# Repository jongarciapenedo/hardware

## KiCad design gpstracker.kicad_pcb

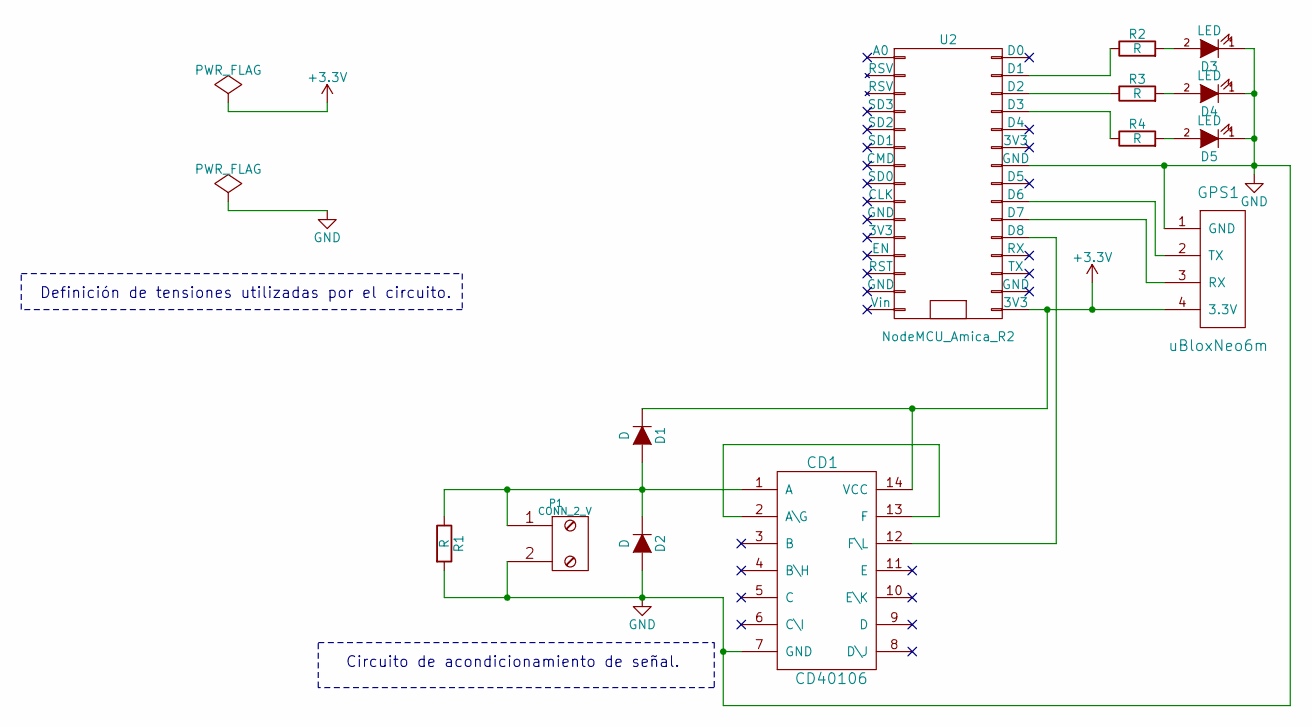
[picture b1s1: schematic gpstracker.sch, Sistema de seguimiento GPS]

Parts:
CD1: CD40106; DIP-14_W7.62mm
D1, D2: D; Diode_DO-35_SOD27_Horizontal_RM10
D3, D4, D5: LED; LED-5MM
GPS1: uBloxNeo6m; Pin_Header_Straight_1x04
P1: CONN_2_V; bornier2_V
R1, R2, R3, R4: R; Resistor_Horizontal_RM10mm
U2: NodeMCU_Amica_R2

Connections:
+3V3: CD1.14 (VCC), D1.1 (K), GPS1.4 (3.3V), U2.16 (3V3)
GND: CD1.7 (GND), D2.2 (A), D3.1 (K), D4.1 (K), D5.1 (K), GPS1.1 (GND), P1.2, R1.2, U2.24 (GND)
unnamed: CD1.1 (A), D1.2 (A), D2.1 (K), P1.1, R1.1
unnamed: CD1.12 (F\L), U2.20 (D8)
unnamed: CD1.2 (A\G), CD1.13 (F)
unnamed: D3.2 (A), R2.2
unnamed: D4.2 (A), R3.2
unnamed: D5.2 (A), R4.2
unnamed: GPS1.2 (TX), U2.22 (D6)
unnamed: GPS1.3 (RX), U2.21 (D7)
unnamed: R2.1, U2.29 (D1)
unnamed: R3.1, U2.28 (D2)
unnamed: R4.1, U2.27 (D3)

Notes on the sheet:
Circuito de acondicionamiento de señal.
Definición de tensiones utilizadas por el circuito.

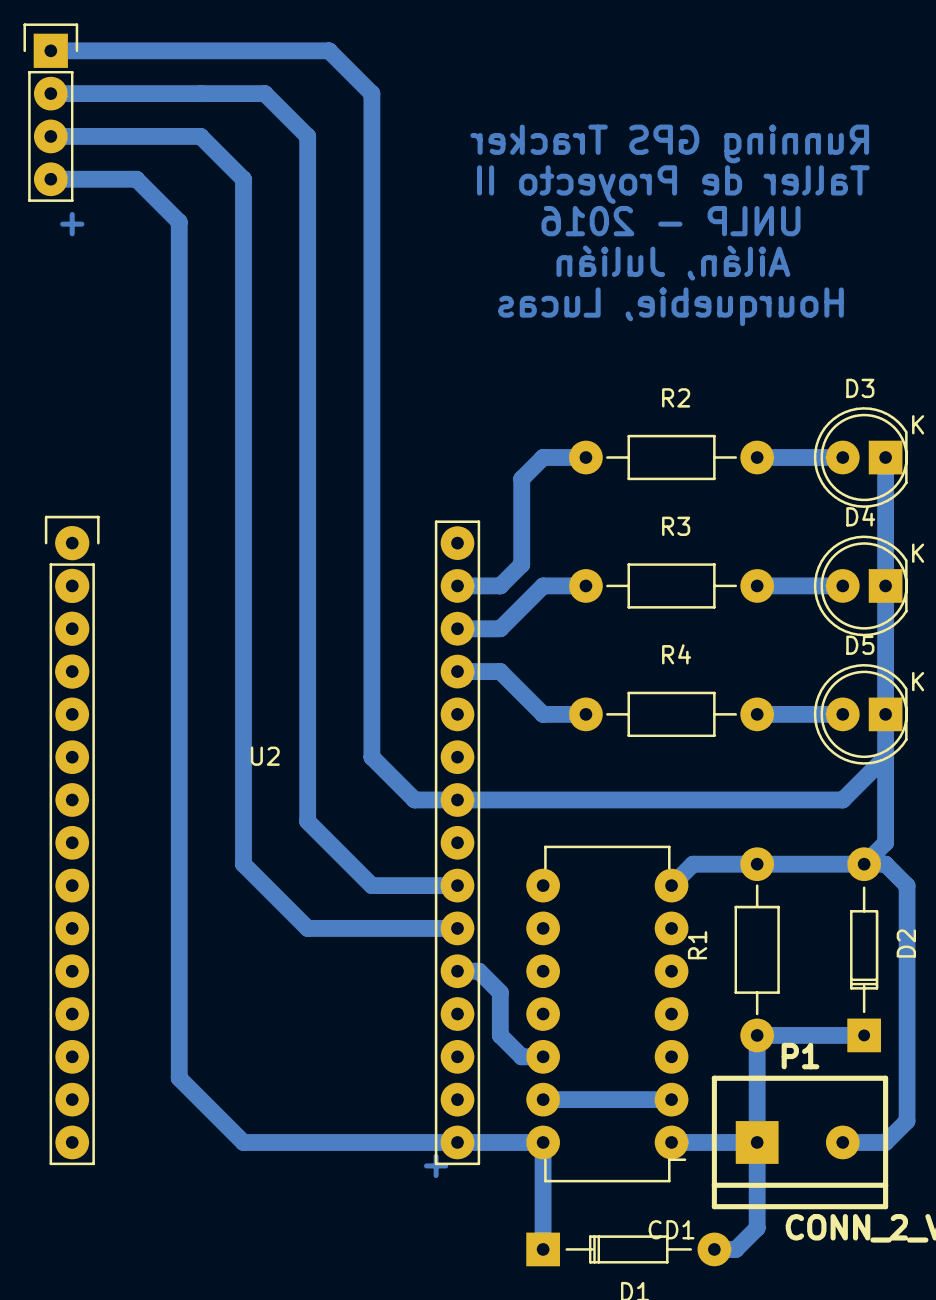
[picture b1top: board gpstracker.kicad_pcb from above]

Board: 2 copper layers, 13 parts (0 on the bottom side), 13 nets.

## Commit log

2016-12-06 Schematic diagram and PCB added.
